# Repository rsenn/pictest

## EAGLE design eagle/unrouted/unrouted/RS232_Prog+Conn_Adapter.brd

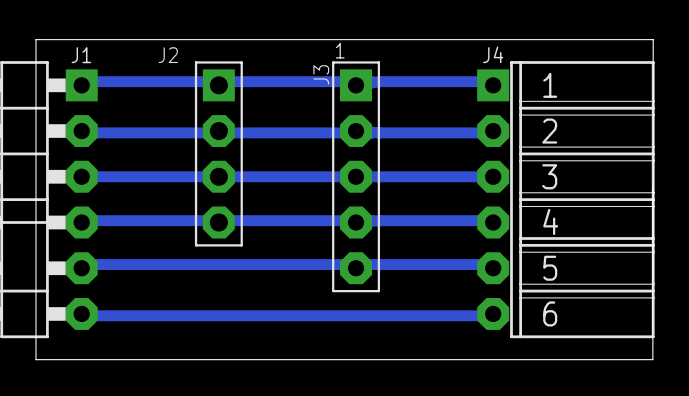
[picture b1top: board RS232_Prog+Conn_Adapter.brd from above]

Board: 2 copper layers, 34.3 x 17.8 mm, 4 parts (0 on the bottom side), 6 nets.

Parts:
J1: COMPORT-6PIN-NEW-6P-NEW-90-L; RS232-6PIN-NEW-90-L
J2: COMPORT-4PIN-NEW-L; RS232-4PIN-NEW-L
J3: CONN-5P; CONN-5P-N
J4: COMPORT-6PIN-NEW-6P-FEM-90; CONN-6P-FEM-90

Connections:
CTS: J1.CTS, J4.6
DTR: J1.DTR, J2.3, J3.3, J4.3
GND: J1.GND, J2.4, J3.4, J4.4
RTS: J1.RTS, J3.5, J4.5
RXD: J1.RXD, J2.1, J3.1, J4.1
TXD: J1.TXD, J2.2, J3.2, J4.2

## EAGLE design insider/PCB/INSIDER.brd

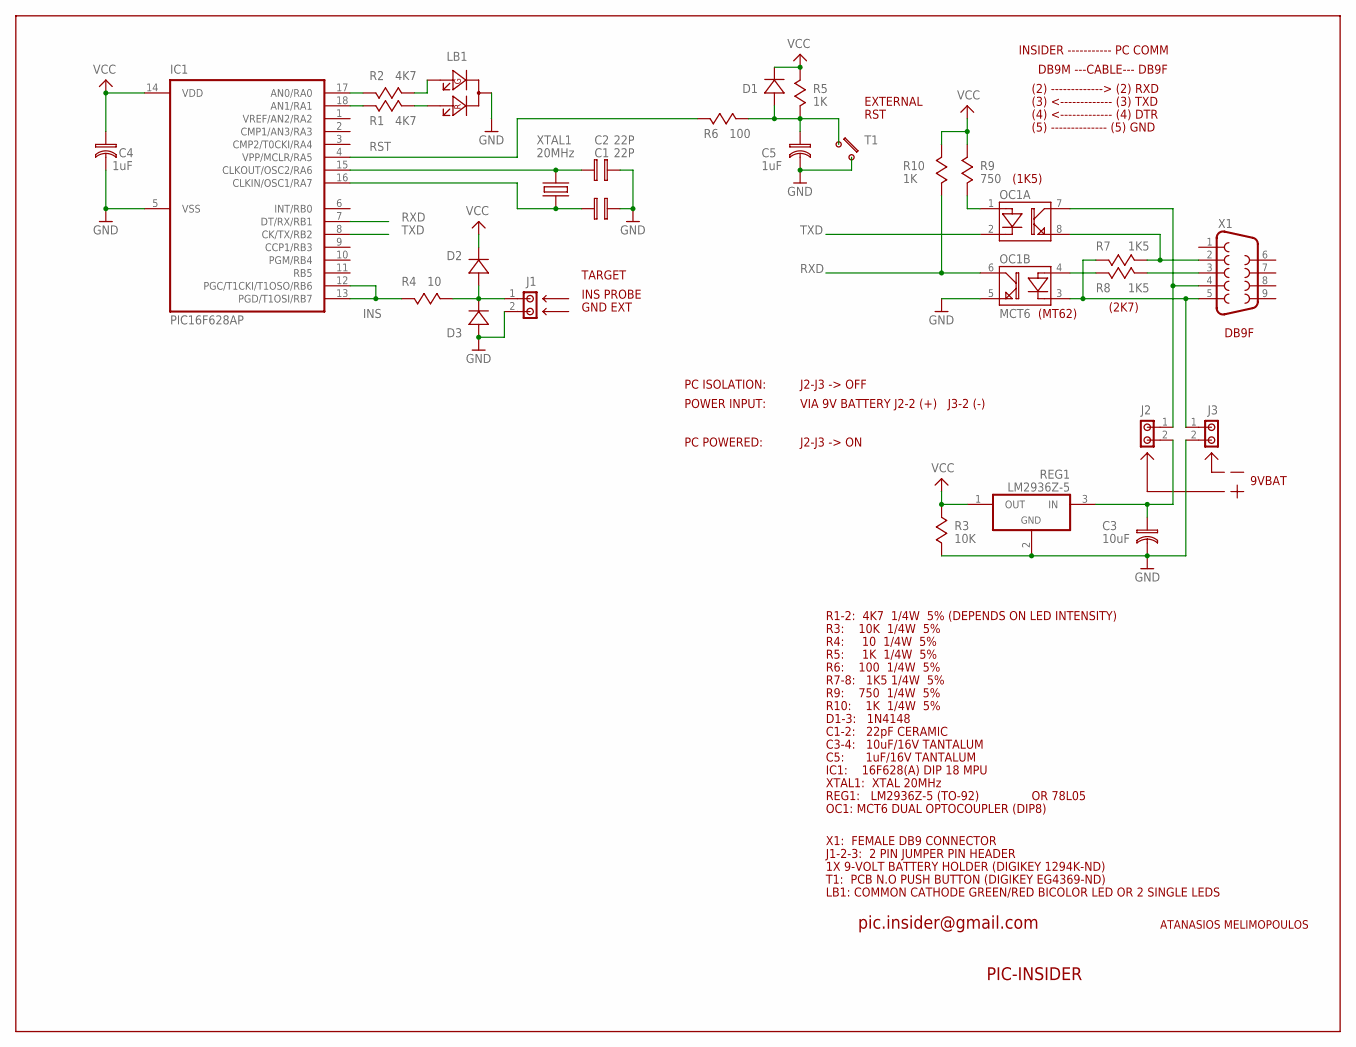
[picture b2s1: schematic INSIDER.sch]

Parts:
C1, C2: 22P; C02
C3: 10uF; CP01
C4, C5: 1uF; CP01
D1, D2, D3: 1N4148; D03
IC1: PIC16F628AP; DIL18
J1, J2, J3: JMP2; JP2
LB1: LEDBIKC; LEDBKC
OC1: MCT6; DIL08
R1, R2: 4K7; R03
R3: 10K; R03
R4: 10; R03
R5, R10: 1K; R03
R6: 100; R03
R7, R8: 1K5; R03
R9: 750; R03
REG1: LM2936Z-5; TO92A
T1: TEC3; TEC3L
X1: F09D
XTAL1: 20MHz; HC49V

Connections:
GND: C1.P$2 (2), C2.P$2 (2), C3.P$2 (2), C4.P$2 (2), C5.P$2 (2), D3.P$1 (A), IC1.5 (VSS), J1.2, J3.2, LB1.K, OC1.5 (E), R3.P$2 (2), REG1.2 (GND), T1.4
INS: IC1.12 (PGC/T1CKI/T1OSO/RB6), IC1.13 (PGD/T1OSI/RB7), R4.P$1 (1)
unnamed: J3.1, OC1.3 (K), R7.P$2 (2), X1.5
unnamed: OC1.8 (E), R7.P$1 (1), X1.2
unnamed: J2.1, OC1.7 (C), X1.4
unnamed: R8.P$1 (1), X1.3
unnamed: OC1.4 (A), R8.P$2 (2)
unnamed: OC1.1 (A), R9.P$1 (1)
unnamed: D2.P$1 (A), D3.P$2 (K), J1.1, R4.P$2 (2)
unnamed: C2.P$1 (1), IC1.15 (CLKOUT/OSC2/RA6), XTAL1.1
unnamed: C1.P$1 (1), IC1.16 (CLKIN/OSC1/RA7), XTAL1.2
unnamed: IC1.17 (AN0/RA0), R2.P$2 (2)
unnamed: LB1.R (A1), R1.P$1 (1)
unnamed: LB1.G (A2), R2.P$1 (1)
unnamed: IC1.18 (AN1/RA1), R1.P$2 (2)
unnamed: C5.P$1 (1), D1.P$1 (A), R5.P$2 (2), R6.P$2 (2), T1.1
unnamed: C3.P$1 (1), J2.2, REG1.3 (IN)
RST: IC1.4 (VPP/MCLR/RA5), R6.P$1 (1)
RXD: IC1.7 (DT/RX/RB1), OC1.6 (C), R10.P$1 (1)
TXD: IC1.8 (CK/TX/RB2), OC1.2 (K)
VCC: C4.P$1 (1), D1.P$2 (K), D2.P$2 (K), IC1.14 (VDD), R3.P$1 (1), R5.P$1 (1), R9.P$2 (2), R10.P$2 (2), REG1.1 (OUT)

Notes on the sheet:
EXTERNAL
RST
PIC-INSIDER
ATANASIOS MELIMOPOULOS
9VBAT
GND EXT
INS PROBE
PC ISOLATION:
J2-J3 -> OFF
POWER INPUT:
VIA 9V BATTERY J2-2 (+) J3-2 (-)
PC POWERED:
J2-J3 -> ON
TARGET
R3: 10K 1/4W 5%
R6: 100 1/4W 5%
R1-2: 4K7 1/4W 5% (DEPENDS ON LED INTENSITY)
R5: 1K 1/4W 5%
R9: 750 1/4W 5%
R7-8: 1K5 1/4W 5%
R10: 1K 1/4W 5%
C1-2: 22pF CERAMIC
C3-4: 10uF/16V TANTALUM
REG1: LM2936Z-5 (TO-92)
OR 78L05
OC1: MCT6 DUAL OPTOCOUPLER (DIP8)
IC1: 16F628(A) DIP 18 MPU
XTAL1: XTAL 20MHz
J1-2-3: 2 PIN JUMPER PIN HEADER
1X 9-VOLT BATTERY HOLDER (DIGIKEY 1294K-ND)
LB1: COMMON CATHODE GREEN/RED BICOLOR LED OR 2 SINGLE LEDS
X1: FEMALE DB9 CONNECTOR
(2) -------------> (2) RXD
(3) <------------- (3) TXD
(4) <------------- (4) DTR
(5) -------------- (5) GND
INSIDER ----------- PC COMM
DB9M ---CABLE--- DB9F
DB9F
pic.insider@gmail.com

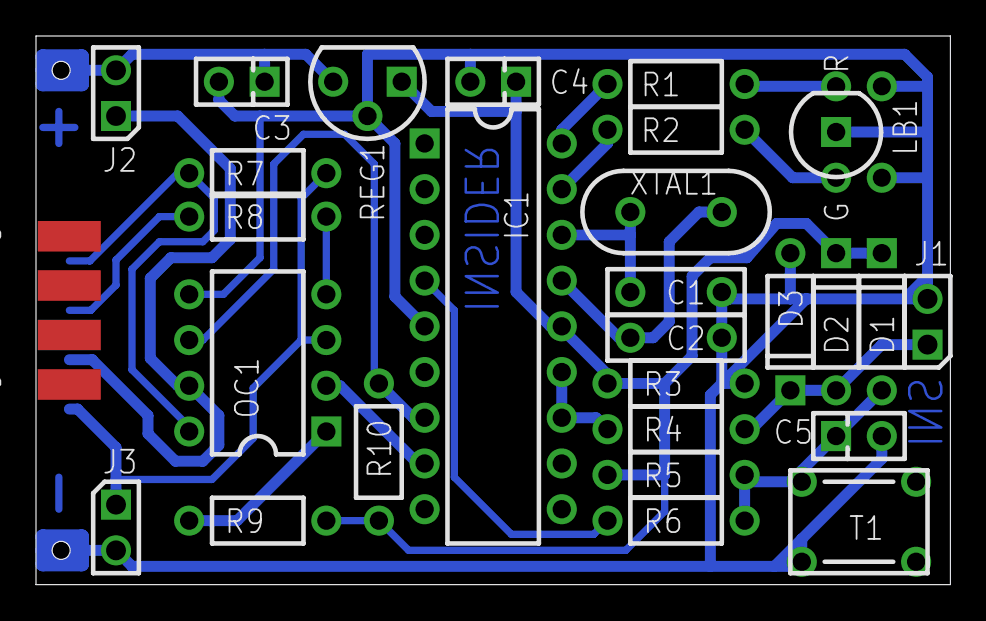
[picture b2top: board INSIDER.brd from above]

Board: 2 copper layers, 50.8 x 30.5 mm, 28 parts (1 on the bottom side), 21 nets.
